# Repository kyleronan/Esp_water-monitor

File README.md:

# Water Monitor

A DIY Home Assistant addon and ESP32-based smart water shut-off valve.
Tracks pressure and flow, learns your home's normal usage, runs scheduled leak
tests, and lets you cut off water to the house from anywhere — without
subscriptions, cloud polling, or trips to the crawl space.

## Background

This started as a hobby project. I wasn't happy with the commercial options
(Moen Flo, StreamLabs Control) — they polled the internet for things that
should work locally, and put basic features behind subscriptions. I also got
tired of crawling under the house every winter to shut off water to the
irrigation, and wanted something I could trigger from an app or a wall switch.

So I built one. It's not as pretty or compact as the off-the-shelf products,
but it has most of the same basic features and runs entirely on my own LAN.

A few design choices worth knowing about up front:

- **Manual override matters.** From day one this had to work with physical
  switches and indicator lights, not just the web UI. If the network is down,
  if I'm not home, if Home Assistant is misbehaving — anyone in the house
  can still open or close the valve.
- **Two circuits.** Main (whole house) plus irrigation. The irrigation valve
  is the one I shut off for winter; having it on a separate circuit makes
  the seasonal routine a one-tap operation.
- **Overbuilt by choice.** Three-piece stainless steel ball valves (serviceable,
  lead-free, more trustworthy than the brass valves on AliExpress), motorised
  actuators with a manual override for power outages, separate pressure
  transducers and flow meters per circuit. You could absolutely build this
  with cheaper parts — most of the firmware doesn't care.
- **Cost-conscious sourcing.** Most components came from AliExpress because the
  same parts from local plumbing/HVAC suppliers were 10× the price. Links to
  what I actually used will go in `docs/` once the hardware build guide is
  written.
- **PCB caveat.** This was my first SMD design. The current revision works,
  but I have a small pile of boards on my shelf that don't. The board is
  optimised for *my* situation, not for manufacturing efficiency or BOM cost.

## On the code

I should be upfront about how this got built. I'm an amateur C coder at best,
and my prior web experience tops out at script-kiddie HTML and Java tinkering.
The firmware was within reach — I had a basically functional firmware and the
valve sitting in the basement "ready" for testing since August 2025 — but the
prospect of writing the Home Assistant addon, with its FastAPI backend, async
WebSockets, Jinja2 templates, SQLite migrations, and clustering algorithms, kept
stalling out against my ADHD. It sat on the shelf for a long time.

So I leaned on AI heavily and did a fair amount of vibe coding to get the
addon to a state where it's actually usable. Originally I figured this whole
project was just for me, but along the way I realised I should at least flesh
it out enough that someone else could build on the idea if they wanted to.
That's why the addon code is more polished than I'd ever have produced on my
own — and also why it might have rough edges only an experienced developer
would have caught.

If you find bugs or design choices that look weird, that's probably why. PRs
welcome.

## TL;DR

I made a thing. It mostly works. If you want to copy it or improve on it,
that's great. I'm probably not going to build another one for myself.

## What it does

- **Real-time monitoring** — pressure and flow on the main and irrigation
  circuits, displayed in the units you choose (L/min · gal/min · ft³/min ·
  m³/min, and PSI · bar · kPa)
- **Learned baseline** — 14-day calibration period during which the addon
  watches your normal usage patterns. When training ends, the Fixtures
  page lists the clusters that were detected; you confirm or remove them,
  then activate the circuit to start anomaly detection (or auto-activates
  after 7 days of no review).
- **Scheduled micro leak tests** — closes each valve in turn at the
  statistically quietest hour of the day, monitors pressure decay, and notifies
  on failure
- **Fixture identification** — clusters water events by their pressure and
  flow signatures to identify individual fixtures (toilets, showers, taps,
  appliances). Live in v0.2.0; naming UI complete; merge-clusters UI and
  ESP-side waveform enrichment added in v0.2.1.
- **Event detail modal** — every event in the History list opens an
  inspector with trigger type, peak flow, propagation delay, anomaly score
  and (with firmware v3.7+) an embedded waveform chart. Events can be
  re-assigned to a fixture or ignored from this view.
- **Degraded-supply guard** (v0.2.2) — detects when the municipal supply
  is pulsing (paddlewheel flow sensors produce garbage under those
  conditions). Affected events are flagged, given an envelope-smoothed
  volume so daily totals stay sensible, and excluded from clustering. The
  Dashboard shows a banner and the History page has a filter.
- **Per-circuit valve type** (v0.2.2) — Setup and Settings let you mark
  each circuit as 2-port (standard) or 3-port (drain-capable for
  winterization). 3-port circuits automatically skip the micro leak test
  (the drain port reads as a constant leak); the schedule is preserved
  if you ever switch back.
- **Runtime flow-meter calibration** (v0.2.2) — pulses-per-litre is a
  per-circuit Home Assistant number entity (NVS-backed, survives OTA), so
  any flow meter works without a firmware edit. A guided **calibration
  helper** (Settings → Flow Meter → Calibrate) measures the true
  pulses-per-litre from a bucket test or a whole-house municipal-meter
  reading — showing each run, their average and range, with an editable,
  safety-gated value before you apply.
- **Anomaly detection** (v0.2.2, Phase 2.3) — flags events that deviate from
  the learned baseline (volume percentiles + per-fixture envelopes) and can
  notify or auto-shut-off, guarded so a thin/young baseline degrades to
  notify-only.
- **Away mode** — pauses learning while unoccupied, automatically toggled
  from your existing HA presence entities
- **Mobile push notifications** for all alerts via HA's `notify.mobile_app_*`
  services, with per-target backoff after repeated failures so a broken
  mobile_app integration doesn't spam the logs.
- **Full backup and restore** — three-tier backup (Quick Restore JSON, History
  Archive SQLite, Full ZIP) with restore-from-backup in the setup wizard
- **Auto dark mode** — the UI follows your OS / browser appearance
  preference automatically. No toggle, no setup.

## Repository structure

This is a Home Assistant addon repository. It also contains the firmware
and the documentation.

```
.
├── repository.yaml      # HA addon repository metadata
├── water_monitor/       # The addon itself (HA expects this at the root)
│   ├── config.yaml
│   ├── Dockerfile
│   ├── icon.png         # Addon icon (128 × 128) — shown on HA addon card
│   ├── logo.png         # Addon logo (250 × 100) — shown on HA store detail page
│   ├── CHANGELOG.md
│   └── app/
├── firmware/            # ESPHome firmware for the ESP32-S3-WROOM-1
├── docs/                # Hardware build notes, pinouts, parts list, and
│                        #   PIPELINE.md — how a drop of water becomes a number
└── ruff.toml            # The one lint rule, enforced from the test suite
```

The test suite, the analysis tools and the release scripts are kept out of
version control (see `.gitignore`), so a fresh clone has none of them.

## Installation

### Addon

1. In Home Assistant: **Settings → Add-ons → Add-on Store**
2. Open the three-dot menu (top right) → **Repositories**
3. Paste this repository's URL:
   ```
   https://github.com/kyleronan/Esp_water-monitor
   ```
4. Click **Add**, then close the dialog
5. The **Water Monitor** addon will appear in the store — click it and **Install**
6. Open the addon's web UI and follow the setup wizard

Updates are delivered automatically — when a new version is pushed to this
repository, the HA addon store will offer the update.

### Hardware

You'll need the ESP32-S3-WROOM-1 board (custom PCB), motorised ball valves
with end-stop signalling, pressure transducers, and pulse-output flow meters.

> **If your home has a pressure boosting pump or well pump system**, install
> the addon's flow and pressure sensors *downstream* of the pump (between the
> pump output and the house plumbing). Sensors placed upstream see pump cycling
> artifacts that mask individual fixture pressure signatures, making the
> fixture identification feature in v0.2.x unreliable. Downstream placement is
> also what every reasonable installation diagram recommends regardless of
> monitoring.

PCB design files (KiCad + Gerbers), bill of materials, build guide, and bring-up checklist are in [`docs/hardware/`](docs/hardware/).

### Firmware

1. Copy `firmware/secrets.yaml.example` to `firmware/secrets.yaml` and fill
   in the five values (API encryption key, OTA password, fallback-AP
   password, web UI username + password). See
   [`firmware/README.md`](firmware/README.md) for the key-generation
   snippet and the security model.
2. Flash `firmware/esp-water-shut-off-3_14.yaml` (v3.14.0) to your
   ESP32-S3-WROOM-1 using ESPHome.
3. Make sure the device is added to Home Assistant before installing the
   addon.
4. The setup wizard will discover the device automatically.

Before tagging a firmware release, run
`python scripts/check_firmware_release.py` — it parses the YAML and
fails if any credential is missing or if `dashboard_import` still
points at a mutable branch ref.

## Access control

**Read this before you install.** The add-on ships with `panel_admin: false`
in `water_monitor/config.yaml`. That is deliberate, but it has a consequence
worth stating plainly:

> **Every Home Assistant user on your instance can open the Water Monitor
> panel — not just HA administrators.**

Home Assistant's `panel_admin` option is what normally hides an add-on's
sidebar panel from non-admin users. This add-on turns it off so that
household members who are not HA admins can still see water usage, and
enforces its own three-tier model *inside* the panel instead:

| Role | Who gets it | What they can do |
|---|---|---|
| **admin** | every Home Assistant administrator, auto-detected | everything |
| **operator** | an in-app allow-list — **Settings → Access** (admins only) | read-only, **plus opening and closing the main valve** for emergencies |
| **viewer** | every other HA user — this is the default | read-only: Dashboard, History, Water Use, Device status |

How it is enforced:

- Roles derive from the `X-Remote-User-Id` header the Supervisor's ingress
  proxy injects. The add-on is ingress-only, which is what makes that header
  trustworthy — **do not expose port 8765 directly**, as that bypasses the
  proxy that supplies the identity.
- Enforcement is server-side, default-deny, at a single middleware
  chokepoint (`water_monitor/app/auth.py`); it is not a UI-hiding trick.
- The HA admin list is cached last-known-good and refreshed every 10 minutes,
  so an HA hiccup cannot silently downgrade a real admin.
- `bootstrap_admin_user_id` is the lockout escape hatch if no admin can be
  resolved.

**If you would rather restrict the whole UI to HA administrators**, set
`panel_admin: true` in `water_monitor/config.yaml` and rebuild the add-on.
The in-panel roles keep working; the panel simply stops being reachable by
non-admins at all.

## Project status

| Phase | Scope | Status |
|---|---|---|
| **0.1.x** | Core monitoring, leak detection, calibration, display units | Shipped |
| **0.2.0** | Fixture identification — clustering engine live, naming UI complete | Shipped |
| **0.2.1** | ESP-side waveform capture & feature enrichment, event detail modal, merge-clusters UI, Basic/Advanced settings split, auto dark mode, hardware docs (PCB v1.2a) | Shipped |
| **0.2.2** | Runtime per-circuit flow-meter PPL + guided flow-calibration helper (bucket / municipal), Phase 2.3 anomaly detection, degraded-supply guard, per-circuit valve type (2-port / 3-port), per-session CSRF refactor, autocorrelation correctness fix, firmware release-gate script, migration transaction safety, async/blocking SQLite audit, live-capture reliability fixes (importer catch-up checkpoint + stuck no-flow phantom close) | Shipped |
| **0.3.0** | Role-based access control — viewer / operator / admin (see [Access control](#access-control)) | Shipped |
| **0.3.1** | Pressure-aware classification that survives a change in water supply, full booster-pump support, a learned per-home classifier, and a long run of volume-accounting fixes. Per-circuit pressure-sensor calibration **infrastructure** shipped in firmware 3.14 (eight `pressure_cal_*` substitutions + a documented bench procedure) — performing the calibration on a given install is a manual hardware step | Shipping incrementally (currently `0.3.1-dev64`, unreleased) |
| **0.3.x** | esp_idf framework migration with a proper top-level task watchdog (the arduino framework this firmware uses does not expose one) | Planned |
| **0.4.x** | Native Home Assistant integration (alongside the addon, eventually replacing the WebSocket bridge for users who prefer pip-installable components) | Planned |

Firmware ships on its own version line and has its own entries in the same
changelog (currently **3.14.0**).

See [`water_monitor/CHANGELOG.md`](water_monitor/CHANGELOG.md) for detailed
release notes.

## License

MIT — see `LICENSE` file. Use it, modify it, sell it, build a better one,
whatever you like. Attribution is appreciated but not required.

## Contributing

This repository is in active development; the API and database schema may
change between minor versions. If you build one and find bugs or have ideas,
issues and PRs are welcome — though responses may be slow given this is a
side project.

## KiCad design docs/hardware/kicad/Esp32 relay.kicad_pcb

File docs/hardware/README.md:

# Hardware Documentation

This folder documents the ESP32 Water Valve Controller hardware build.

Use the board labels from the PCB and KiCad files throughout the hardware docs:

- Valve 1
- Valve 2

Software may allow custom names later, but the hardware build guide uses the physical board labels.

## Main documents

- `bom.md` - simplified builder-facing BOM
- `pinouts.md` - board connector pinouts
- `breakaway-front-panel-controls.md` - optional manual/auto front-panel control board
- `bring-up-checklist.md` - first power-up and test checklist

## Hardware Build Guide

This is a high-level build guide for the ESP32 Water Valve Controller hardware.

### Build order

1. Inspect the bare PCB.
2. Assemble the PCB.
3. Inspect solder joints and orientation-sensitive parts.
4. Separate the breakaway front-panel control section if it will be used.
5. Mount the main PCB in the enclosure.
6. Mount the breakaway control section and panel LEDs on the enclosure front panel.
7. Wire the 12 V DIN rail power supply and DIN terminal blocks.
8. Wire Valve 1 and Valve 2.
9. Wire the flow and pressure sensors.
10. Power up without plumbing pressure and run the bring-up checklist.
11. Test valve open/close behavior.
12. Test sensor readings.
13. Perform plumbing tests and calibration.

## Build photos

These photos document the prototype, assembly, enclosure wiring, plumbing test, pressure calibration, front panel, and breakaway switch wiring.

### Photo index

| Photo | Description |
| --- | --- |
| [Early prototyping](images/early-prototyping.jpg) | Early hardware prototyping before the final enclosure layout. |
| [Soldering complete](images/soldering-complete.jpg) | Assembled PCB after soldering. |
| [First enclosure wiring and testing](images/first-enclosure-wiring-and-testing.jpg) | Initial wiring inside the enclosure during testing. |
| [First plumbing test](images/first-plumbing-test-hose-floor-drain.jpg) | Initial plumbing test using a hose and floor drain. |
| [Pressure sensor calibration](images/pressure-sensor-calibration-analog-gauge.jpg) | Pressure sensor calibration using an analog pressure gauge. |
| [Inside of enclosure](images/inside-enclosure.jpg) | Internal enclosure layout with mounted electronics and wiring. |
| [Breakaway switch board wiring](images/breakaway-switch-board-bypass-wiring-enclosure-door.jpg) | Breakaway switch/control board bypass wiring mounted on the enclosure door. |
| [Outside of enclosure with LEDs](images/outside-enclosure-leds-wip.jpg) | Front of the enclosure showing panel LEDs. Work in progress; final labels still needed. |
| [ESP32-S3 WROOM-1 pinout](images/esp32s3_wroom1_pinout.png) | Pin reference diagram for the ESP32-S3 WROOM-1 module used in this build. |

### Gallery

#### Early prototyping

Early hardware prototyping before the final enclosure layout.

#### Soldering complete

Assembled PCB after soldering.

#### First enclosure wiring and testing

Initial wiring inside the enclosure during testing.

#### First plumbing test

Initial plumbing test using a hose and floor drain.
#### Pressure sensor calibration

Pressure sensor calibration using an analog pressure gauge.

#### Inside of enclosure

Internal enclosure layout with mounted electronics and wiring.

#### Breakaway switch board wiring

Breakaway switch/control board bypass wiring mounted on the enclosure door.

#### Outside of enclosure with LEDs

Front of the enclosure showing panel LEDs. Work in progress; final labels still needed.

#### ESP32-S3 WROOM-1 pinout

Pin reference diagram for the ESP32-S3 WROOM-1 module used in this build.

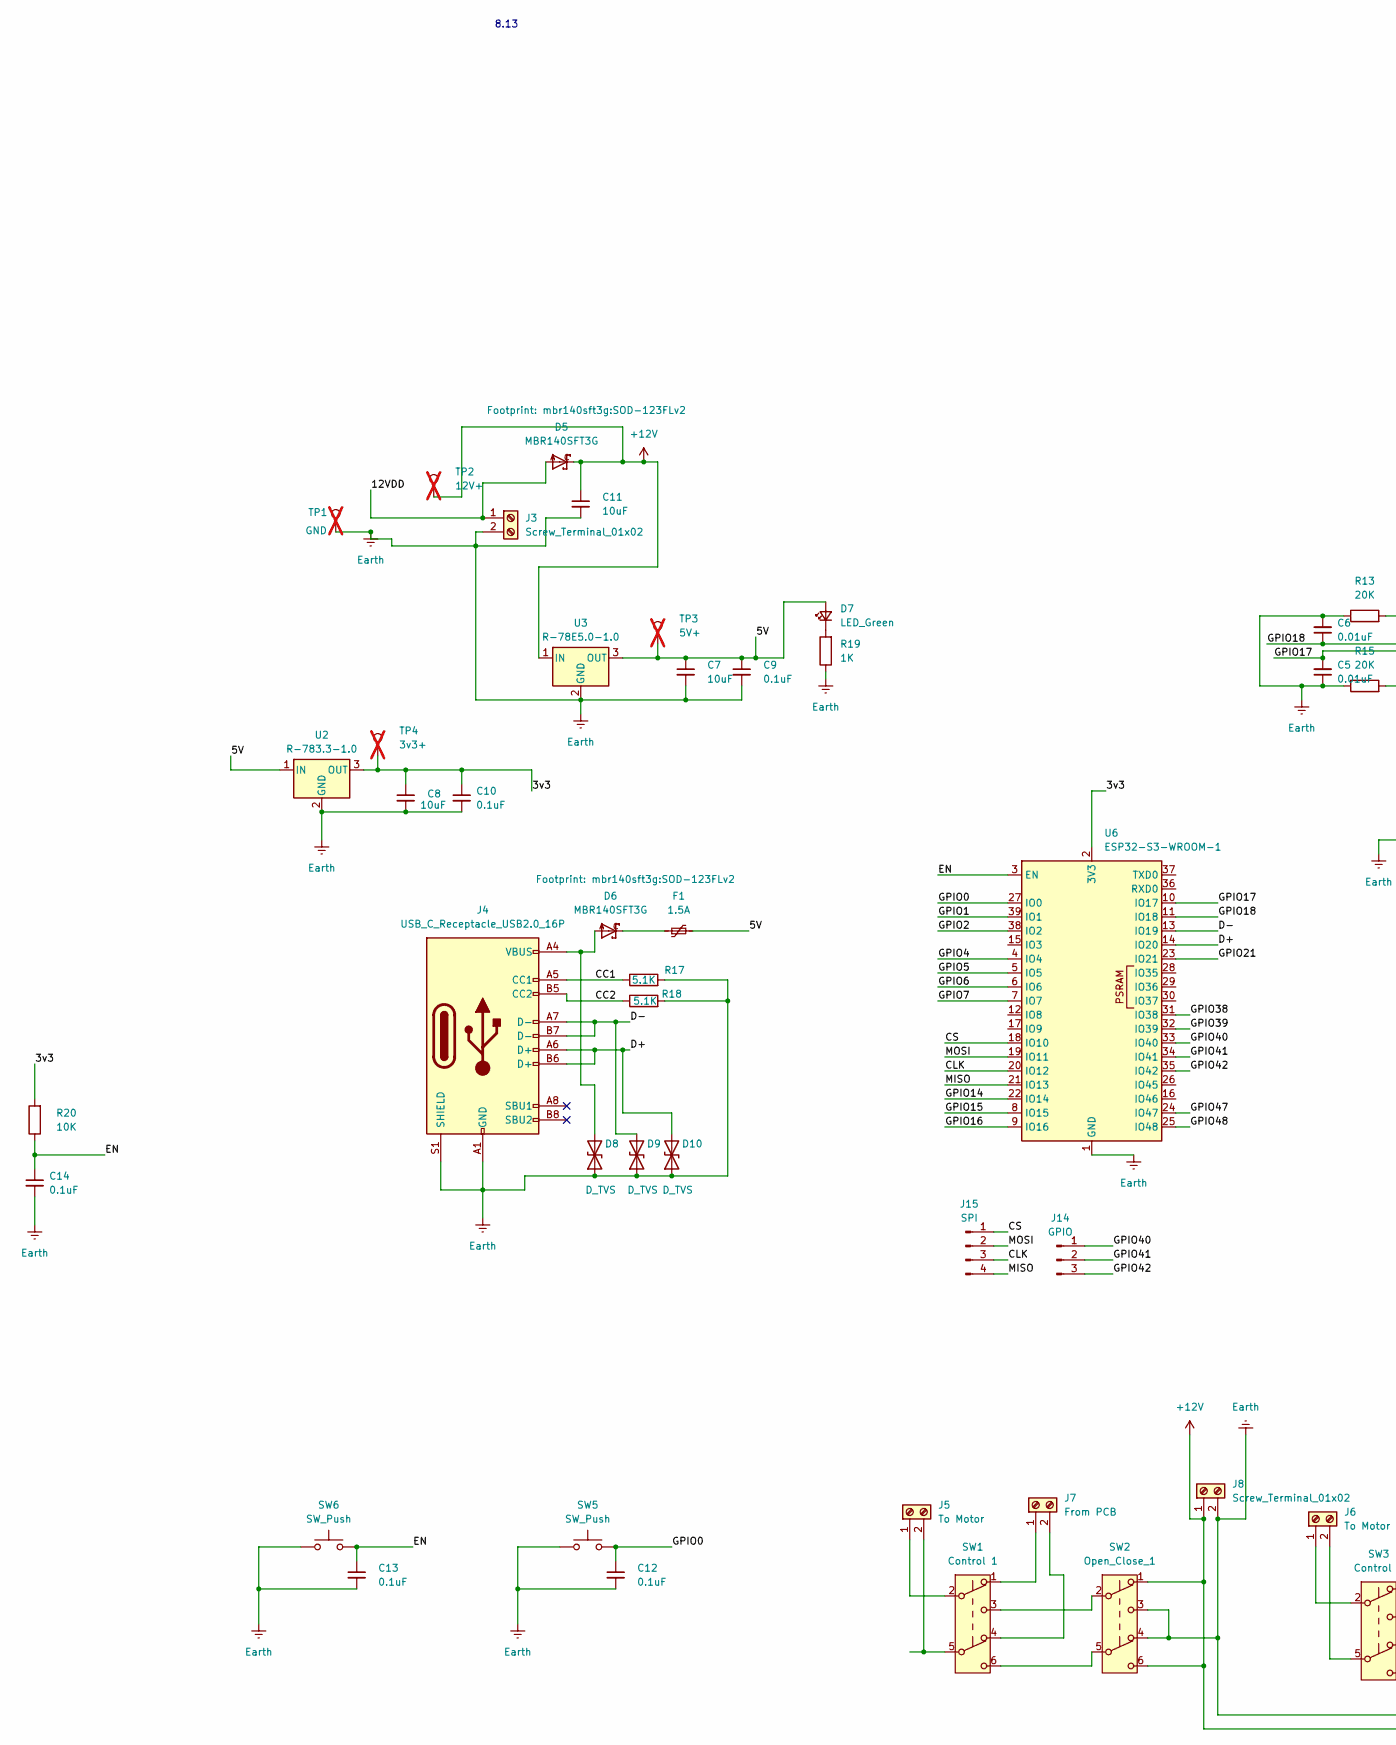
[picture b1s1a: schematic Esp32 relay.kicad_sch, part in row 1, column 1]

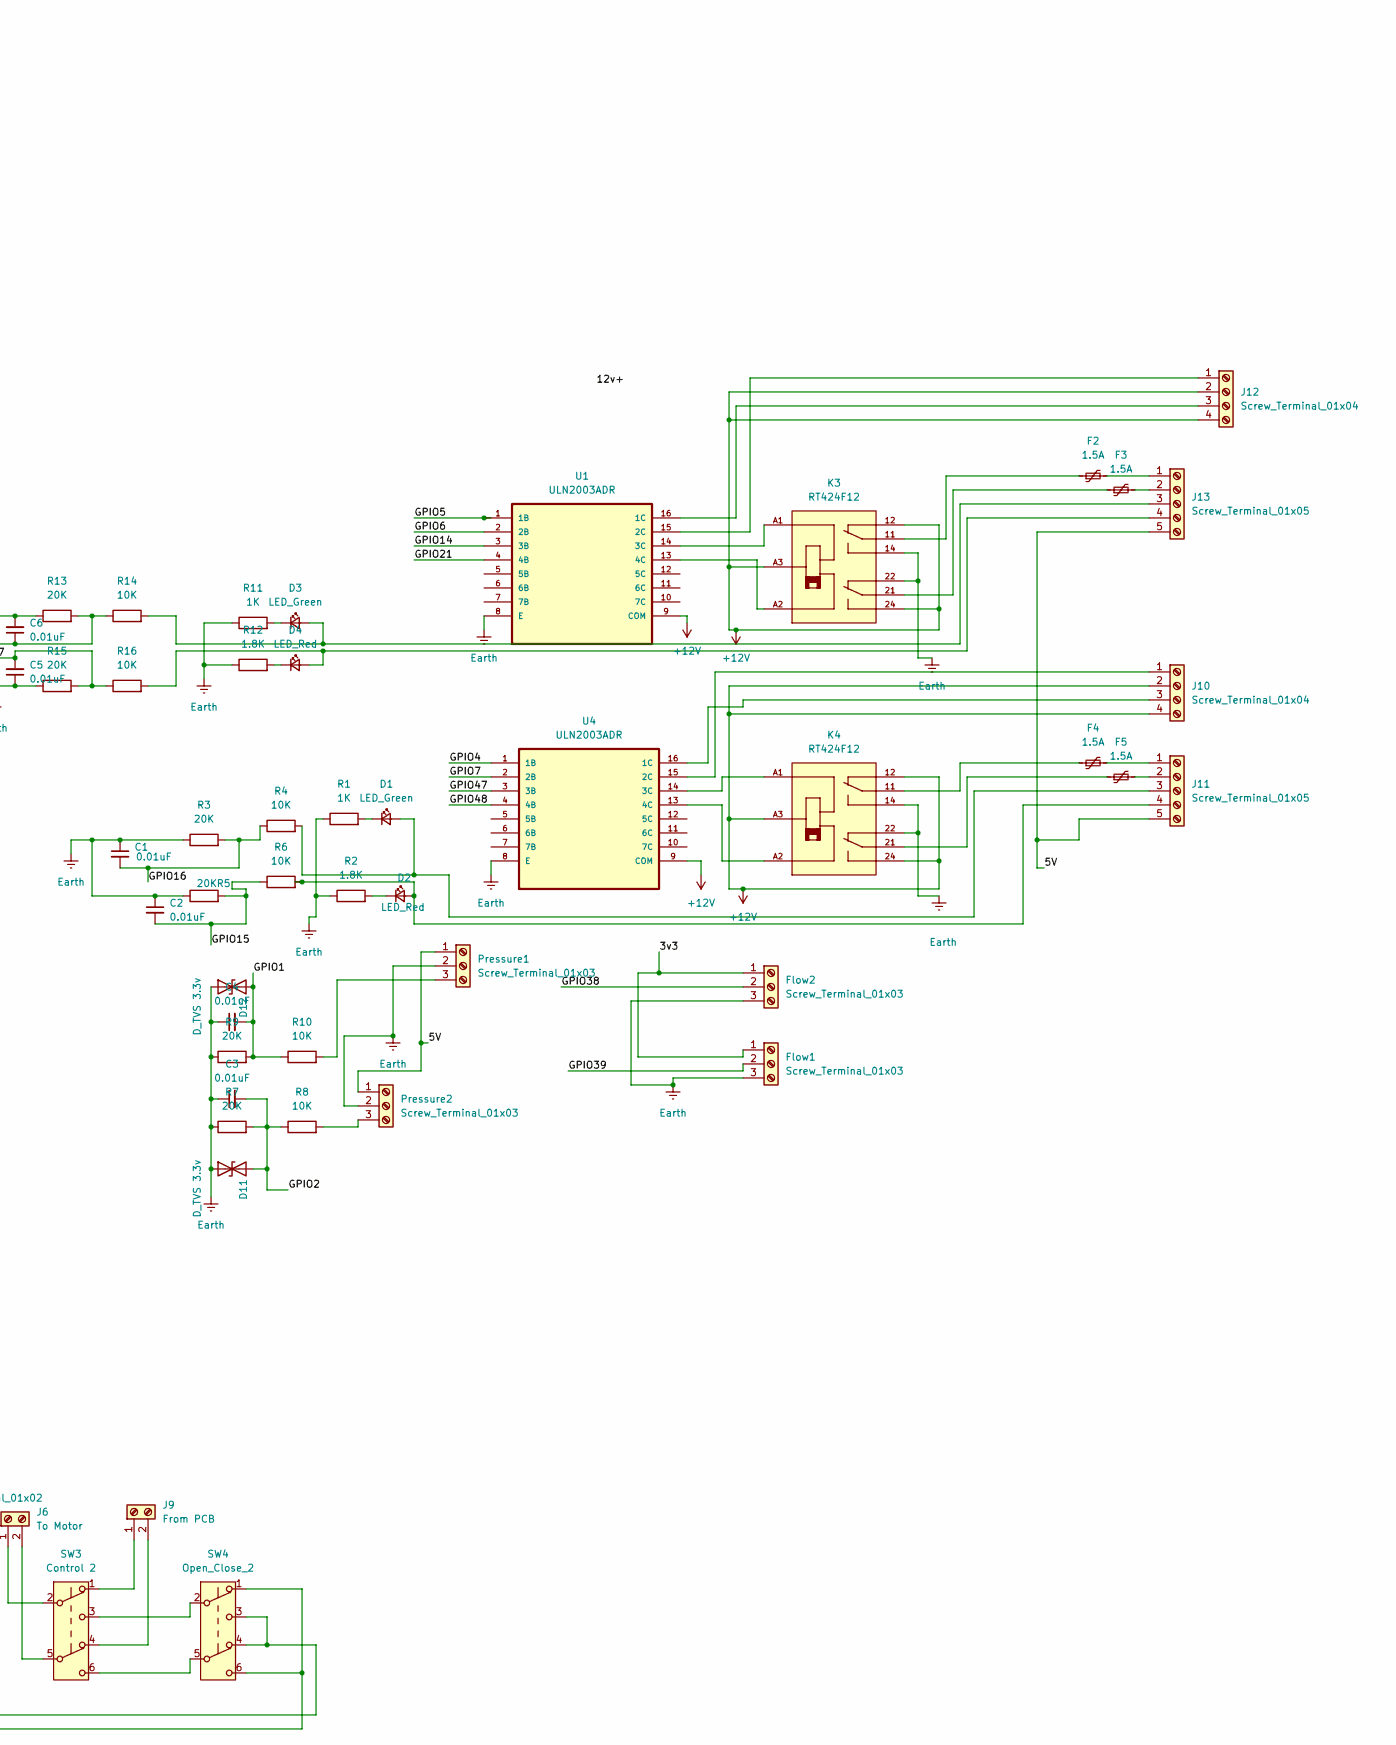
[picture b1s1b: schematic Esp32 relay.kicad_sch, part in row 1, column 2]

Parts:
C1, C2, C3, C4, C5, C6: 0.01uF; C_0603_1608Metric
C7, C8, C11: 10uF; C_0603_1608Metric
C9, C10, C12, C13, C14: 0.1uF; C_0603_1608Metric
D1, D3, D7: LED_Green; LED_0603_1608Metric; Part# B1931NG--20D001114U1930
D2, D4: LED_Red; LED_0603_1608Metric; Part# B1931URO-20D000114U1930
D5, D6: MBR140SFT3G; SOD-123FLv2; Part# MBR140SFT3G
D8, D9, D10: D_TVS; D_SOD-323_HandSoldering
D11, D12: D_TVS 3.3v; D_SOD-323_HandSoldering
F1, F2, F3, F4, F5: 1.5A; Fuse_1812_4532Metric_Pad1.30x3.40mm_HandSolder; Part# 5923-0ZCG0150AF2CCT-ND
Flow1, Flow2: Screw_Terminal_01x03; TerminalBlock_Phoenix_MKDS-1,5-3_1x03_P5.00mm_Horizontal; Part# 1935174
J3, J8: Screw_Terminal_01x02; TerminalBlock_Phoenix_MKDS-1,5-2_1x02_P5.00mm_Horizontal; Part# 1935161
J4: USB_C_Receptacle_USB2.0_16P; USB_C_Receptacle_GCT_USB4105-xx-A_16P_TopMnt_Horizontal
J5, J6: To Motor; TerminalBlock_Phoenix_MKDS-1,5-2_1x02_P5.00mm_Horizontal; Part# 1935161
J7, J9: From PCB; TerminalBlock_Phoenix_MKDS-1,5-2_1x02_P5.00mm_Horizontal; Part# 1935161
J10, J12: Screw_Terminal_01x04; TerminalBlock_Phoenix_MKDS-1,5-4_1x04_P5.00mm_Horizontal; Part# 1935187
J11, J13: Screw_Terminal_01x05; TerminalBlock_Phoenix_MKDS-1,5-5_1x05_P5.00mm_Horizontal; Part# 1935190
J14: GPIO; PinSocket_1x03_P2.54mm_Vertical
J15: SPI; PinSocket_1x04_P2.54mm_Vertical
K3, K4: RT424F12; TE_5-1393243-4; PARTREV 1116
Pressure1, Pressure2: Screw_Terminal_01x03; TerminalBlock_Phoenix_MKDS-1,5-3_1x03_P5.00mm_Horizontal; Part# 1935174
R1, R11, R19: 1K; R_0805_2012Metric; Part# RMCF0805FT1K80CT-ND
R2, R12: 1.8K; R_0805_2012Metric
R3, R5, R7, R9, R13, R15: 20K; R_0805_2012Metric
R4, R6, R8, R10, R14, R16, R20: 10K; R_0805_2012Metric
R17, R18: 5.1K; R_0805_2012Metric
SW1: Control 1; ANT23SECQE DPDT; Part# 100DP3T1B3M2QEH-ND
SW2: Open_Close_1; ANT23SECQE DPDT; Part# 100DP3T1B3M2QEH-ND
SW3: Control 2; ANT23SECQE DPDT; Part# 100DP3T1B3M2QEH-ND
SW4: Open_Close_2; ANT23SECQE DPDT; Part# 100DP3T1B3M2QEH-ND
SW5, SW6: SW_Push; SW PTS636 SP50 SMTR LFS; Part# PTS636 SP50 SMTR LFS
TP1: GND; TestPoint_Pad_1.5x1.5mm; not fitted
TP2: 12V+; TestPoint_Pad_1.5x1.5mm; not fitted
TP3: 5V+; TestPoint_Pad_1.5x1.5mm; not fitted
TP4: 3v3+; TestPoint_Pad_1.5x1.5mm; not fitted
U1, U4: ULN2003ADR; SOIC127P600X175-16N; Part# ULN2003ADR
U2: R-783.3-1.0; Converter_DCDC_RECOM_R-78E-0.5_THT; Part# 945-1036-ND
U3: R-78E5.0-1.0; Converter_DCDC_RECOM_R-78E-0.5_THT; Part# 945-2201-ND
U6: ESP32-S3-WROOM-1; Part# 5407-ESP32-S3-WROOM-1-N8R2CT-ND

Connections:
+12V: C11.1, D5.C, J8.1, J10.2, J10.4, J12.2, J12.4, K3.12, K3.24, K3.A3, K4.12, K4.24, K4.A3, SW2.1 (A), SW2.6 (C), SW4.1 (A), SW4.6 (C), TP2.1 (1_1), U1.9 (COM), U3.1 (IN), U4.9 (COM)
/3v3: C8.1, C10.1, Flow1.1, Flow2.1, R20.2, TP4.1 (1_1), U2.3 (OUT), U6.2 (3V3)
/5V: C7.1, C9.1, D7.2 (A), F1.2, J11.5, J13.5, Pressure1.1, Pressure2.1, TP3.1 (1_1), U2.1 (IN), U3.3 (OUT)
/12VDD: D5.A, J3.1
/CC1: J4.A5 (CC1), R17.1
/CC2: J4.B5 (CC2), R18.1
/CLK: J15.3, U6.20 (IO12)
/CS: J15.1, U6.18 (IO10)
/D+: D10.2 (A2), J4.A6 (D+), J4.B6 (D+), U6.14 (IO20)
/D-: D9.2 (A2), J4.A7 (D-), J4.B7 (D-), U6.13 (IO19)
/EN: C13.1, C14.1, R20.1, SW6.2, U6.3 (EN)
/GPIO0: C12.1, SW5.2, U6.27 (IO0)
/GPIO1: C4.2, D12.2 (A2), R9.2, R10.1, U6.39 (IO1)
/GPIO2: C3.2, D11.2 (A2), R7.2, R8.1, U6.38 (IO2)
/GPIO4: U4.1 (1B), U6.4 (IO4)
/GPIO5: U1.1 (1B), U6.5 (IO5)
/GPIO6: U1.2 (2B), U6.6 (IO6)
/GPIO7: U4.2 (2B), U6.7 (IO7)
/GPIO14: U1.3 (3B), U6.22 (IO14)
/GPIO15: C2.2, R5.2, R6.1, U6.8 (IO15)
/GPIO16: C1.2, R3.2, R4.1, U6.9 (IO16)
/GPIO17: C5.2, R15.2, R16.1, U6.10 (IO17)
/GPIO18: C6.1, R13.2, R14.1, U6.11 (IO18)
/GPIO21: U1.4 (4B), U6.23 (IO21)
/GPIO38: Flow2.2, U6.31 (IO38)
/GPIO39: Flow1.2, U6.32 (IO39)
/GPIO40: J14.1, U6.33 (IO40)
/GPIO41: J14.2, U6.34 (IO41)
/GPIO42: J14.3, U6.35 (IO42)
/GPIO47: U4.3 (3B), U6.24 (IO47)
/GPIO48: U4.4 (4B), U6.25 (IO48)
/MISO: J15.4, U6.21 (IO13)
/MOSI: J15.2, U6.19 (IO11)
Earth: C1.1, C2.1, C3.1, C4.1, C5.1, C6.2, C7.2, C8.2, C9.2, C10.2, C11.2, C12.2, C13.2, C14.2, D8.1 (A1), D9.1 (A1), D10.1 (A1), D11.1 (A1), D12.1 (A1), Flow1.3, Flow2.3, J3.2, J4.A1 (GND), J4.A12 (GND), J4.B1 (GND), J4.B12 (GND), J4.S1 (SHIELD), J8.2, K3.14, K3.22, K4.14, K4.22, Pressure1.2, Pressure2.2, R1.1, R2.1, R3.1, R5.1, R7.1, R9.1, R11.1, R12.1, R13.1, R15.1, R17.2, R18.2, R19.1, SW2.3 (C), SW2.4 (A), SW4.3 (C), SW4.4 (A), SW5.1, SW6.1, TP1.1 (1_1), U1.8 (E), U2.2 (GND), U3.2 (GND), U4.8 (E), U6.1 (GND), U6.40 (GND), U6.41 (GND)
unnamed: D1.2 (A), J11.3, R4.2
unnamed: D1.1 (K), R1.2
unnamed: D2.2 (A), J11.4, R6.2
unnamed: D2.1 (K), R2.2
unnamed: D3.2 (A), J13.3, R14.2
unnamed: D3.1 (K), R11.2
unnamed: D4.2 (A), J13.4, R16.2
unnamed: D4.1 (K), R12.2
unnamed: D6.C, F1.1
unnamed: D7.1 (K), R19.2
unnamed: D6.A, D8.2 (A2), J4.A4 (VBUS), J4.A9 (VBUS), J4.B4 (VBUS), J4.B9 (VBUS)
unnamed: F2.1, K3.11
unnamed: F3.1, K3.21
unnamed: F4.1, K4.11
unnamed: F5.1, K4.21
unnamed: J5.1, SW1.2 (B)
unnamed: J5.2, SW1.5 (B)
unnamed: J6.1, SW3.2 (B)
unnamed: J6.2, SW3.5 (B)
unnamed: J7.1, SW1.1 (A)
unnamed: J7.2, SW1.4 (A)
unnamed: J9.1, SW3.1 (A)
unnamed: J9.2, SW3.4 (A)
unnamed: J10.1, U4.15 (2C)
unnamed: J10.3, U4.16 (1C)
unnamed: F4.2, J11.1
unnamed: F5.2, J11.2
unnamed: J12.1, U1.15 (2C)
unnamed: J12.3, U1.16 (1C)
unnamed: F2.2, J13.1
unnamed: F3.2, J13.2
unnamed: Pressure1.3, R10.2
unnamed: Pressure2.3, R8.2
unnamed: SW1.3 (C), SW2.2 (B)
unnamed: SW1.6 (C), SW2.5 (B)
unnamed: SW3.3 (C), SW4.2 (B)
unnamed: SW3.6 (C), SW4.5 (B)
unnamed: K3.A1, U1.14 (3C)
unnamed: K3.A2, U1.13 (4C)
unnamed: K4.A1, U4.14 (3C)
unnamed: K4.A2, U4.13 (4C)

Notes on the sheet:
8.13

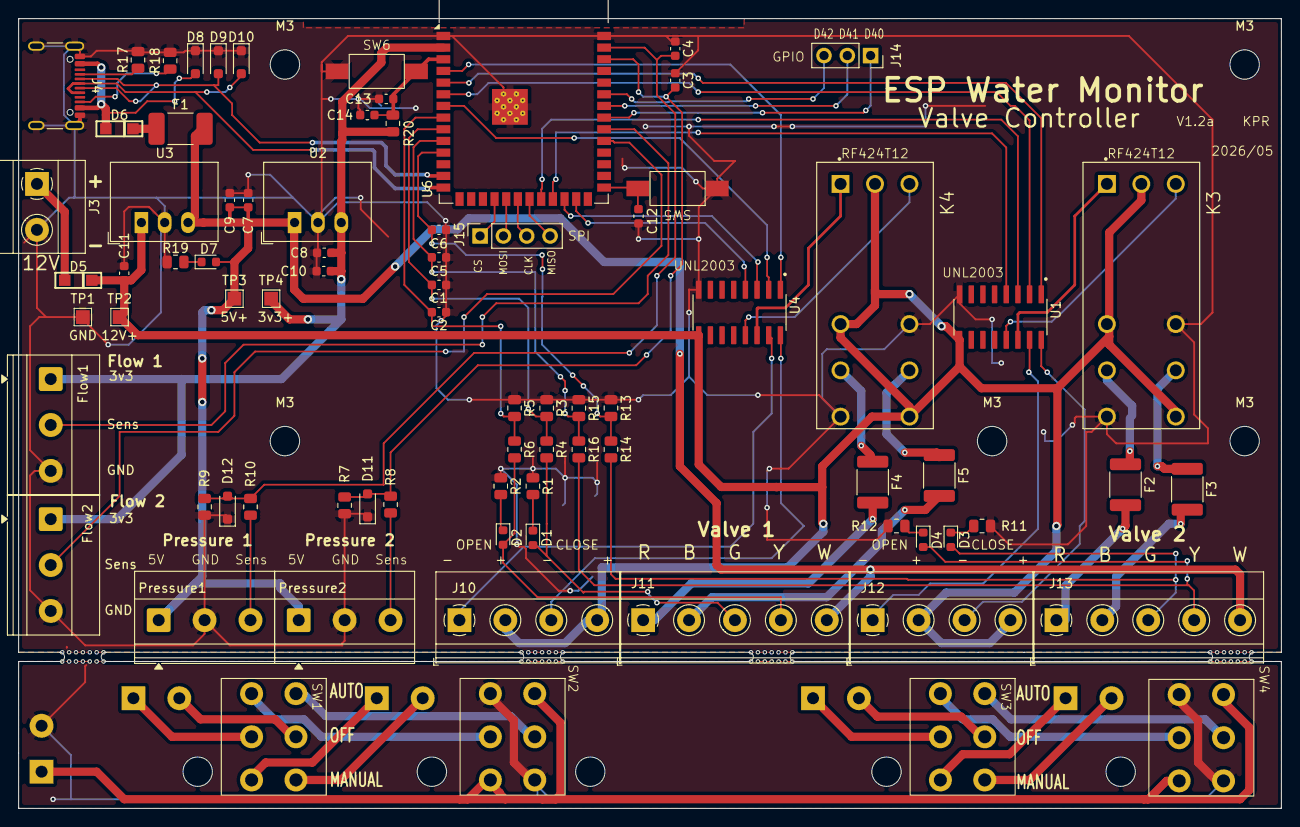
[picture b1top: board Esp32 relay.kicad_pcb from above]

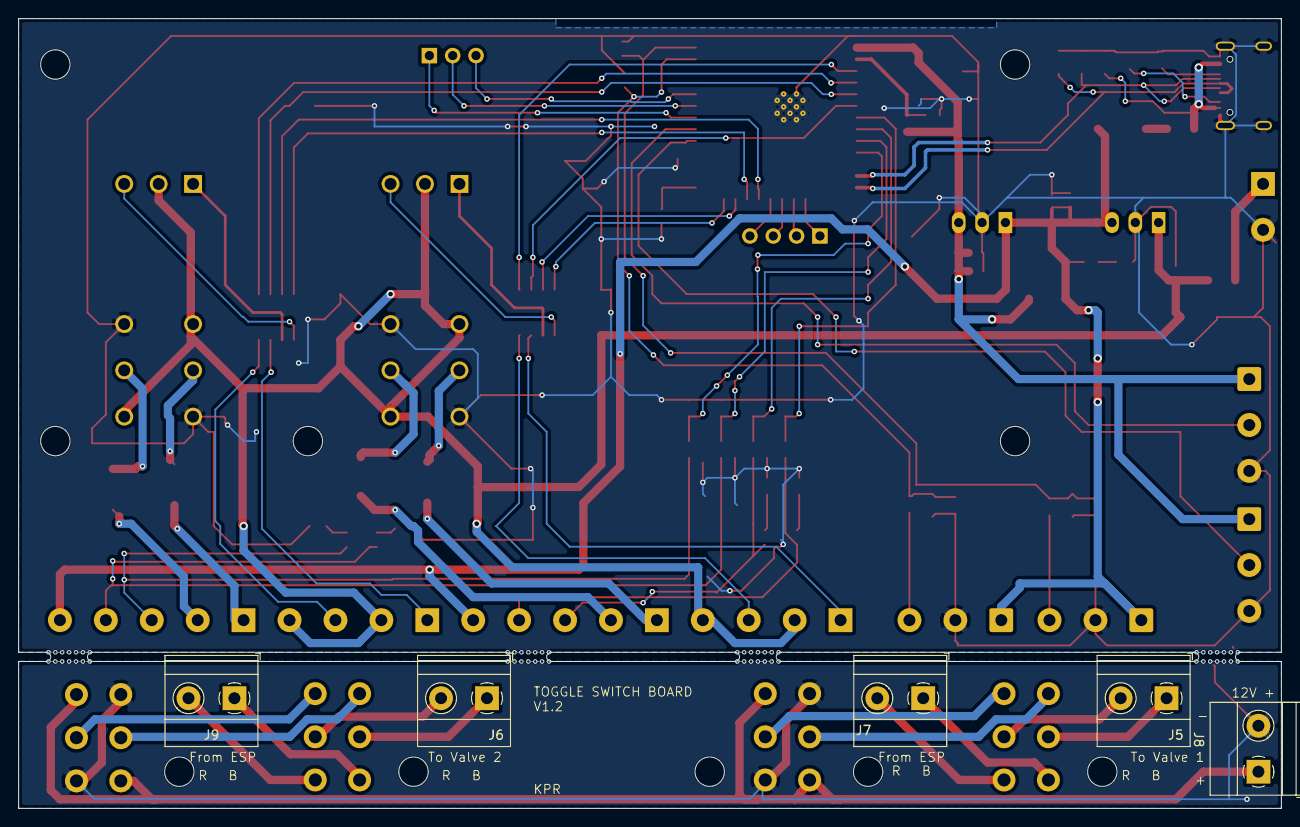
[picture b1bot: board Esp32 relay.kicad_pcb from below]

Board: 2 copper layers, 137.5 x 86.0 mm, 95 parts (5 on the bottom side), 75 nets.

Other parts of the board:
M3, M3#2, M3#3, M3#4, M3#5, M3#6, M3#7, M3#8, M3#9, M3#10: MountingHole_3.2mm_M3

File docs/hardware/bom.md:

# Bill of Materials

This is the simplified builder-facing BOM for the PCB and related hardware.


## Important BOM notes

- The KiCad source files included in this package use `470R` for the installed resistor value.
- For 4-position terminal groups, the build uses two Phoenix Contact `1935161` 2-position terminal blocks.
- The confirmed quantity for Phoenix Contact `1935161` terminal blocks is 9 per build.
- Majority of PCB components were purchased from Digikey

## PCB BOM

| Qty | References | Value | Footprint | Part | Supplier Part # | Notes |
| --- | --- | --- | --- | --- | --- | --- |
| 6 | C1, C2, C3, C4, C5, C6 | `0.01uF` | `Capacitor_SMD:C_0603_1608Metric` | KEMET C0603C103J3HACTU | `399-C0603C103J3HACTUCT-ND` |  |
| 5 | C9, C10, C12, C13, C14 | `0.1uF` | `Capacitor_SMD:C_0603_1608Metric` | TDK C1608X8R1E104K080AA | `445-2500-1-ND` |  |
| 3 | C7, C8, C11 | `10uF` | `Capacitor_SMD:C_0603_1608Metric` | Samsung Electro-Mechanics CL10X106MO8NRNC | `1276-6769-1-ND` |  |
| 2 | Led1, Led2 | `Conn_01x04_Socket` | `Connector_PinSocket_2.54mm:PinSocket_1x04_P2.54mm_Vertical` | Phoenix Contact 1935161 | `277-1667-ND` | Uses two 2-position 1935161 terminal blocks per 4-position connector group |
| 2 | J1, J2 | `Conn_01x05_Pin` | `Connector_PinSocket_2.54mm:PinSocket_1x05_P2.54mm_Vertical` | Phoenix Contact 1935161 | `277-1667-ND` | Uses PCB terminal blocks, confirmed total 1935161 quantity is 9 per build |
| 2 | J7, J9 | `From PCB` | `TerminalBlock_Phoenix:TerminalBlock_Phoenix_MKDS-1,5-2_1x02_P5.00mm_Horizontal` | Phoenix Contact 1935161 | `277-1667-ND` |  |
| 1 | J14 | `GPIO` | `Connector_PinSocket_2.54mm:PinSocket_1x03_P2.54mm_Vertical` |  |  |  |
| 1 | J15 | `SPI` | `Connector_PinSocket_2.54mm:PinSocket_1x04_P2.54mm_Vertical` | Phoenix Contact 1935161 | `277-1667-ND` | Uses two 2-position 1935161 terminal blocks per 4-position connector group |
| 2 | J3, J8 | `Screw_Terminal_01x02` | `TerminalBlock_Phoenix:TerminalBlock_Phoenix_MKDS-1,5-2_1x02_P5.00mm_Horizontal` | Phoenix Contact 1935161 | `277-1667-ND` |  |
| 2 | J10, J12 | `Screw_Terminal_01x04` | `TerminalBlock_Phoenix:TerminalBlock_Phoenix_MKDS-1,5-4_1x04_P5.00mm_Horizontal` | Phoenix Contact 1935161 | `277-1667-ND` | Uses two 2-position 1935161 terminal blocks per 4-position connector group |
| 2 | J11, J13 | `Screw_Terminal_01x05` | `TerminalBlock_Phoenix:TerminalBlock_Phoenix_MKDS-1,5-5_1x05_P5.00mm_Horizontal` | Phoenix Contact 1935161 | `277-1667-ND` | Uses PCB terminal blocks, confirmed total 1935161 quantity is 9 per build |
| 2 | J5, J6 | `To Motor` | `TerminalBlock_Phoenix:TerminalBlock_Phoenix_MKDS-1,5-2_1x02_P5.00mm_Horizontal` | Phoenix Contact 1935161 | `277-1667-ND` |  |
| 1 | J4 | `USB_C_Receptacle_USB2.0_16P` | `Connector_USB:USB_C_Receptacle_GCT_USB4105-xx-A_16P_TopMnt_Horizontal` | GCT USB4215-03-A | `2073-USB4215-03-ACT-ND` | Verify footprint vs purchased connector |
| 2 | D5, D6 | `MBR140SFT3G` | `mbr140sft3g:SOD-123FLv2` | onsemi MBR140SFT3G | `MBR140SFT3GOSCT-ND` |  |
| 1 | U6 | `ESP32-S3-WROOM-1` | `RF_Module:ESP32-S3-WROOM-1` | Espressif ESP32-S3-WROOM-1-N8R2 | `1965-ESP32-S3-WROOM-1-N8R2-ND` |  |
| 1 | U2 | `R-783.3-1.0` | `Converter_DCDC:Converter_DCDC_RECOM_R-78E-0.5_THT` | Recom Power R-783.3-1.0 | `945-1036-ND` |  |
| 1 | U3 | `R-78E5.0-1.0` | `Converter_DCDC:Converter_DCDC_RECOM_R-78E-0.5_THT` | Recom Power R-78E5.0-1.0 | `945-2201-ND` |  |
| 2 | U1, U4 | `ULN2003ADR` | `ULN2003ADR:SOIC127P600X175-16N` | Texas Instruments ULN2003ADR | `296-1368-1-ND` |  |
| 3 | D1, D3, D7 | `LED_Green` | `LED_SMD:LED_0603_1608Metric` | Harvatek B1931NG--20D001114U1930 | `3147-B1931NG--20D001114U1930CT-ND` |  |
| 2 | D2, D4 | `LED_Red` | `LED_SMD:LED_0603_1608Metric` | Harvatek B1931URO-20D000114U1930 | `3147-B1931URO-20D000114U1930CT-ND` |  |
| 1 | F1 | `1.5A` | `Fuse:Fuse_1812_4532Metric_Pad1.30x3.40mm_HandSolder` | Bel Fuse 0ZCG0150AF2C | `5923-0ZCG0150AF2CCT-ND` |  |
| 4 | Flow1, Flow2, Pressure1, Pressure2 | `Conn_01x03_Pin` | `Connector_PinSocket_2.54mm:PinSocket_1x03_P2.54mm_Vertical` |  |  |  |
| 3 | D8, D9, D10 | `D_TVS` | `Diode_SMD:D_SOD-323_HandSoldering` | Diodes Inc. D5V0F1B2WS-7 | `31-D5V0F1B2WS-7CT-ND` | Verify footprint/package |
| 2 | K3, K4 | `RT424F12` | `RT42f12:TE_5-1393243-4` | TE Connectivity Potter & Brumfield RT424F12 | `RT424F12-ND` |  |
| 7 | R4, R6, R8, R10, R14, R16, R20 | `10K` | `Resistor_SMD:R_0805_2012Metric` | Stackpole RMCF0805FT10K0 | `RMCF0805FT10K0CT-ND` |  |
| 6 | R3, R5, R7, R9, R13, R15 | `20K` | `Resistor_SMD:R_0805_2012Metric` | Stackpole RMCF0805FT20K0 | `RMCF0805FT20K0CT-ND` |  |
| 5 | R1, R2, R11, R12, R19 | `470R` | `Resistor_SMD:R_0805_2012Metric` | Stackpole RMCF0805FT470R | `RMCF0805FT470RCT-ND` |  |
| 2 | R17, R18 | `5.1K` | `Resistor_SMD:R_0805_2012Metric` | Stackpole RMCF0805FT5K10 | `RMCF0805FT5K10CT-ND` |  |
| 1 | SW1 | `Control 1` | `Toggle_switch:ANT23SECQE DPDT` |  |  |  |
| 1 | SW3 | `Control 2` | `Toggle_switch:ANT23SECQE DPDT` |  |  |  |
| 1 | SW2 | `Open_Close_1` | `Toggle_switch:ANT23SECQE DPDT` |  |  |  |
| 1 | SW4 | `Open_Close_2` | `Toggle_switch:ANT23SECQE DPDT` |  |  |  |
| 2 | SW5, SW6 | `SW_Push` | `Push_button_Switch:SW PTS636 SP50 SMTR LFS` | C&K PTS636 SP50 SMTR LFS | `CKN12316-1-ND` |  |
| 1 | TP2 | `12V+` | `TestPoint:TestPoint_Pad_1.5x1.5mm` |  |  |  |
| 1 | TP4 | `3v3+` | `TestPoint:TestPoint_Pad_1.5x1.5mm` |  |  |  |
| 1 | TP3 | `5V+` | `TestPoint:TestPoint_Pad_1.5x1.5mm` |  |  |  |
| 1 | TP1 | `GND` | `TestPoint:TestPoint_Pad_1.5x1.5mm` |  |  |  |

## Enclosure and field hardware


### Pressure sensor

- Supplier: Amazon
- ASIN: `B0CFJ7BN3L` https://www.amazon.com/dp/B0CFJ7BN3L
- Type: 100 PSI pressure transducer
- Thread: 1/8"-27 NPT
- Supply: 5 to 16 V DC
- Output: 0.5 to 4.5 V analog
- Material: 316 stainless steel
- Listed waterproof rating: IP65

#### Pressure sensor wiring

| Wire color | Function |
| --- | --- |
| Red | Supply + |
| Black | Ground |
| Green | Analog sense output |

Pressure sensors are powered from 5 V. The sense output is scaled by a resistor divider before reaching the ESP32 ADC input.

### Flow sensor

- Supplier: AliExpress
- Item: `3256804293371927` https://www.aliexpress.us/item/3256804293371927.html
- Selected version: 5 V version
- Used from the PCB 3.3 V supply because the sensor works down to 3.3 V

#### Flow sensor wiring

| Wire color | Function |
| --- | --- |
| Red | Supply + |
| Black | Ground |
| Yellow | Pulse output |

The flow sensor pulse output connects directly to the ESP32 GPIO input. No voltage divider or extra signal conditioning is needed because the sensor is powered from 3.3 V.

### Valve

- Ball valve item: AliExpress `3256803975349392` https://www.aliexpress.us/item/3256803975349392.html
- Valve motor item: AliExpress `3256804718502721` https://www.aliexpress.us/item/3256804718502721.html
- Size: 3/4 inch
- Control type: CR5 01 / CR501
- Voltage: 12 V DC
- Thread type: NPT
- Material: 304 stainless steel
- Pressure rating: 600 WOG

Verify local plumbing requirements and potable-water suitability before installation.

### Enclosure

- Supplier: Amazon
- ASIN: `B0CSJXTLGZ` https://www.amazon.com/dp/B0CSJXTLGZ
- Style: lockable outdoor weatherproof enclosure
- Size selected: 11.4 in x 7.5 in x 5.5 in
- DIN terminal blocks: Dinkle DK2.5N, 12 to 22 AWG, various colors
- Cable glands: TE Connectivity ENTRELEC `1SNG601161R0000`
- 12 V DIN rail power supply: Ideal Power `56YSD60S-1204500`

### Panel accessories

| Qty | Part | Description |
| ---: | --- | --- |
| 2 | McMaster-Carr `2779K111` | Green 12 V DC quick-disconnect panel LED, 5/16 inch panel cutout |
| 2 | McMaster-Carr `2779K113` | Red 12 V DC quick-disconnect panel LED, 5/16 inch panel cutout |

Quick-disconnect terminals are used for the external panel LED wiring.

### DIN rail power supply

The build uses an Ideal Power `56YSD60S-1204500` 12 V DIN rail power supply.

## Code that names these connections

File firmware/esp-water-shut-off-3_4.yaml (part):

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      - round: 2

  # ---------------------------------------------------------------------------
  # FLOW SENSOR 1 — Main line (GPIO39)
  # Pulse counter connected to a turbine flow meter.
  # Converts pulse frequency to flow rate in litres per minute.
  # Formula: pulses per minute / (6.6 * 60) = L/min
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  #   the timer. The alert duration should be several minutes or more so this
  #   is insignificant relative to the total detection time.
  # ---------------------------------------------------------------------------
  # FLOW SENSOR 1 BASE — Main line (GPIO39)
  # Single pulse_counter on this GPIO — the only component on GPIO39.
  # Reports raw pulses/min (x). internal: true — not exposed to HA.
  # Derived sensors below convert to L/min and detect flow onset.
  #
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  # ---------------------------------------------------------------------------
  - platform: pulse_counter
    pin:
      number: GPIO39
      mode:
        input: true
        pulldown: true    # pulldown prevents floating input causing false counts
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            }

  # ---------------------------------------------------------------------------
  # FLOW SENSOR 1 — Main line (GPIO39, via flow_base_main)
  # Copy of the base pulse counter. Applies unit conversion and smoothing.
  # All safety on_value logic runs here at the smoothed 1s publish rate.
  # ---------------------------------------------------------------------------
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            }

  # ---------------------------------------------------------------------------
  # FLOW SENSOR 2 BASE — Irrigation line (GPIO38)
  # Same architecture as flow_base_main — see comments above.
  # ---------------------------------------------------------------------------
  - platform: pulse_counter
    pin:
      number: GPIO38
      mode:
        input: true
        pulldown: true
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            }

  # ---------------------------------------------------------------------------
  # FLOW SENSOR 2 — Irrigation line (GPIO38, via flow_base_irr)
  # Same configuration as flow sensor 1. Independent fault and valve control.
  # ---------------------------------------------------------------------------
  - platform: copy
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  # FLOW ONSET SENSORS — Main and Irrigation
  #
  # ESPHome 2026.4+ no longer allows multiple components on the same physical
  # GPIO pin. The previous GPIO binary sensor approach (sharing GPIO38/39 with
  # the pulse counters) no longer compiles.
  #
  # Replacement: template binary sensors derived from the smoothed flow rate.
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  # ---------------------------------------------------------------------------
  - platform: gpio
    pin:
      number: GPIO16
      mode:
        input: true
        pullup: true
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
  - platform: gpio
    pin:
      number: GPIO15
      mode:
        input: true
        pullup: true
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  # ---------------------------------------------------------------------------
  - platform: gpio
    pin:
      number: GPIO18
      mode:
        input: true
        pullup: true
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
  - platform: gpio
    pin:
      number: GPIO17
      mode:
        input: true
        pullup: true
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# ---------------------------------------------------------------------------
switch:
  - platform: gpio
    pin: GPIO48
    name: "Relay Open Valve 1"
    id: relay_open_valve1
    internal: true

  - platform: gpio
    pin: GPIO47
    name: "Relay Closed Valve 1"
    id: relay_closed_valve1
    internal: true

  - platform: gpio
    pin: GPIO14
    name: "Relay Open Valve 2"
    id: relay_open_valve2
    internal: true

  - platform: gpio
    pin: GPIO21
    name: "Relay Closed Valve 2"
    id: relay_closed_valve2
    internal: true
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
